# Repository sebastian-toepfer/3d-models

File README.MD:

A repo that contains my hardwares projects.
They are very simple, I am still learning. Most of the names are in German. My kicad stuff are mostly dangerous.

## ⚠️ Legal Disclaimer

This project and all associated hardware, firmware, and design files are provided **without any form of certification or regulatory approval**. They are intended **solely for private, educational, or research use**.

Any use of this project in a commercial, professional, or publicly accessible context may **require certification** (e.g. CE, FCC, RED) and compliance with national and international regulations.

It is **your sole responsibility** to ensure that any use, deployment, or modification of this project complies with applicable laws and technical standards, particularly in regard to **radio frequency emissions, electromagnetic compatibility (EMC), and product safety**.

The authors disclaim any liability for damages, legal issues, or regulatory violations resulting from the use of this project.

## License
until 2025/07/08: [CC0 1.0 Universal](https://creativecommons.org/publicdomain/zero/1.0/)  
from 2025/07/08 mutli licenses, see [LICENSE](LICENSE)

I'm making this move to express that the purpose of this repo is no longer just 3d (creative) content, but also includes PCBs and firmware.

## Structure

| folder                                               | description |
|------------------------------------------------------|-------------|
|projects                                              | contains the project, each is an umbrella to stuff for the same problem |
|projects/Makefile                                     | create the hole project (e.g. generated 3mf, stl or generate step from the pcb, build the firmware, flash firmware) |
|projects/&lt;prjname&gt;/3d                           | contains 3d stuff for the project |
|projects/&lt;prjname&gt;/3d/3mf                       | 3mf files for the project (currently all should be printable) |
|projects/&lt;prjname&gt;/3d/openscad                  | contains the openscad files of the project |
|projects/&lt;prjname&gt;/3d/openscad/libs             | link to the shared 3d libs (see below) |
|projects/&lt;prjname&gt;/3d/openscad/models           | a openscad model with the full assemblied model for the project (like a full case with bottom and top part) |
|projects/&lt;prjname&gt;/3d/openscad/parts            | openscad models which use to create the hole model and must be printed |
|projects/&lt;prjname&gt;/3d/openscad/sharedparts      | link to the shared 3d parts (see below) |
|projects/&lt;prjname&gt;/3d/step                      | step files used by the projekt (like the pcb) |
|projects/&lt;prjname&gt;/3d/stl                       | stl files, some can be printed some are created from the step to be usable in openscad |
|projects/&lt;prjname&gt;/docs                         | some docs |
|projects/&lt;prjname&gt;/docs/assembly                | how to assembly the parts to create the model |
|projects/&lt;prjname&gt;/firmware                     | the source for the firmware |
|projects/&lt;prjname&gt;/firmware/Makefile            | to create and flash the firmware |
|projects/&lt;prjname&gt;/kicad                        | kicad stuff for the project |
|projects/&lt;prjname&gt;/kicad/libraries              | project specific kicad stuff |
|projects/&lt;prjname&gt;/kicad/libraries/footprints   | custom footprints |
|projects/&lt;prjname&gt;/kicad/<kicadproject>         | the kicad project (or project's if we need more than one pcb) for the project |
|projects/&lt;prjname&gt;tools                         | link to shared tools (see below)  |
|shared                                                | stuff has no clean project focus or can be used by more than one project (subfolders should be linked into the projects if needed!)  |
|shared/3d/parts                                       | 3d parts can be used in more than one project  |
|shared/3d/libs                                        | 3d libs or reusable functions  |
|shared/3d/things                                      | 3d models of real existing things (like a speaker, a screen) |
|shared/tools                                          | tools without any project scope (like extract pinmapping from schematic and generate header and board.c) |

all parts are optional, this means a project with only 3d parts must not contains a firmware or a kicad folder.
bigger projects can contains projects it self!

a project should contains at least one Makefile to build it. if no Makefile in a project it means that it not generate or build anything (like tutorials).

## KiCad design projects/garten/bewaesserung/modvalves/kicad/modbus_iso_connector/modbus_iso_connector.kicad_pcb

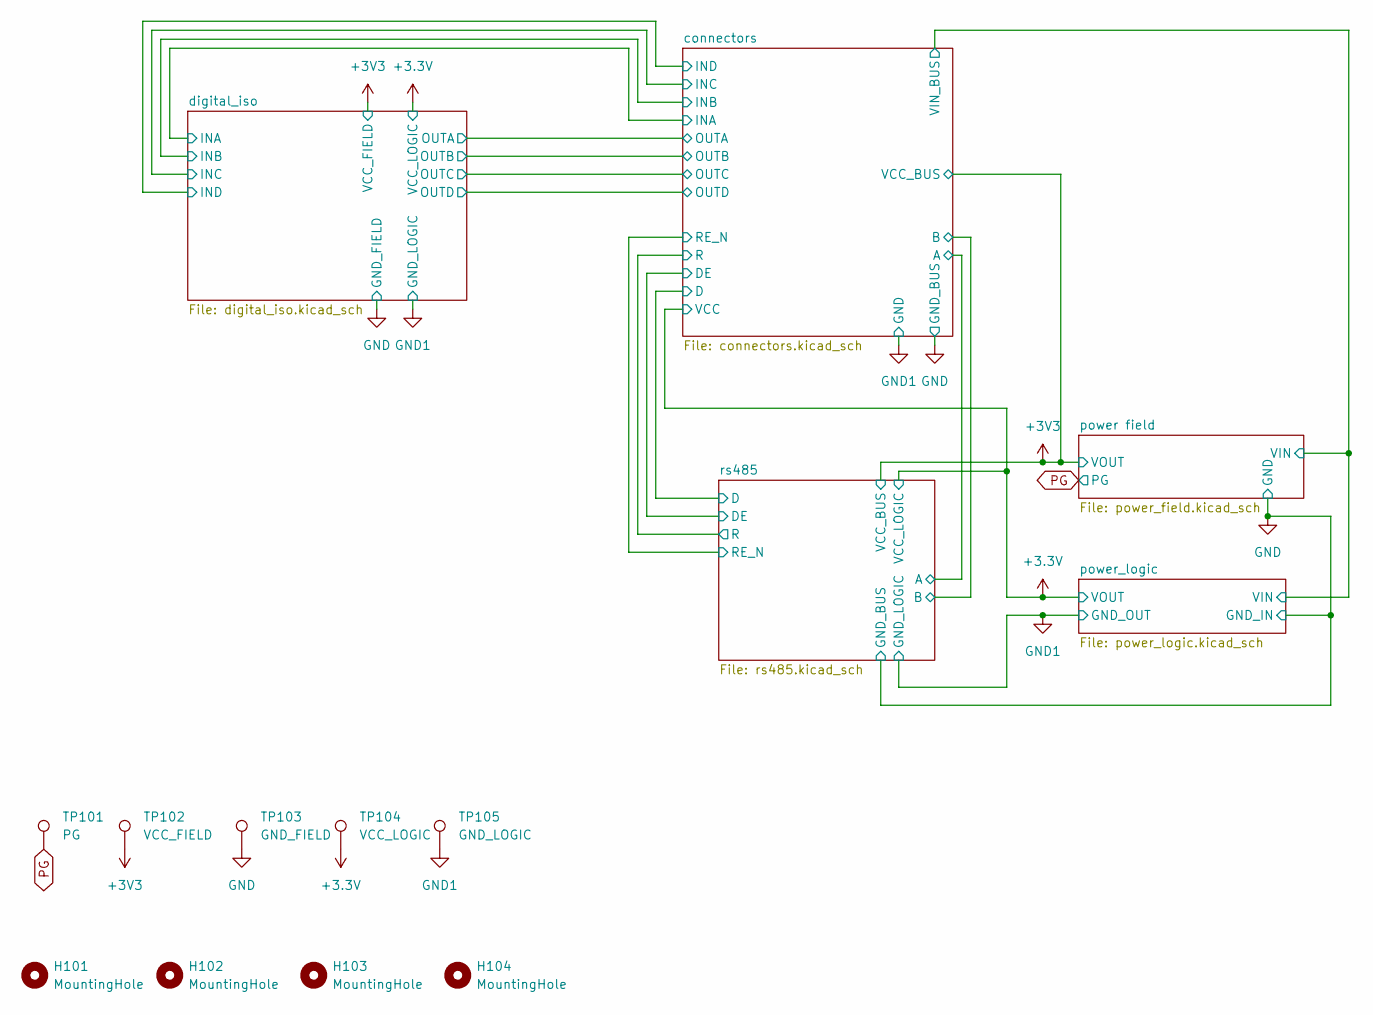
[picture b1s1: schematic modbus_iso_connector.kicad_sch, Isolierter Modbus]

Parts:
H101, H102, H103, H104: MountingHole; MountingHole_3.2mm_M3
TP101: PG; TestPoint_Pad_1.5x1.5mm
TP102: VCC_FIELD; TestPoint_Pad_1.5x1.5mm
TP103: GND_FIELD; TestPoint_Pad_1.5x1.5mm
TP104: VCC_LOGIC; TestPoint_Pad_1.5x1.5mm
TP105: GND_LOGIC; TestPoint_Pad_1.5x1.5mm

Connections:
+3.3V: TP104.1; also elsewhere on the board
+3V3: TP102.1; also elsewhere on the board
GND: TP103.1; also elsewhere on the board
GND1: TP105.1; also elsewhere on the board
PG: TP101.1; also elsewhere on the board

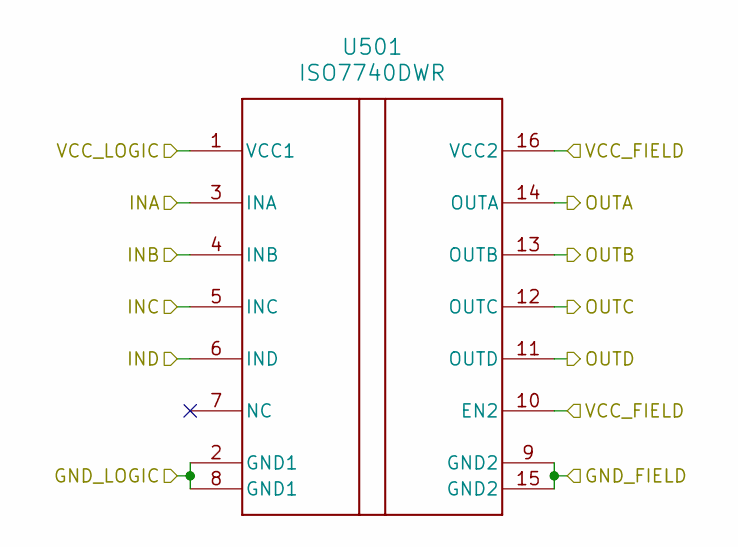
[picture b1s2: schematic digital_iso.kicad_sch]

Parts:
U501: ISO7740DWR; DW0016B_N

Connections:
+3.3V: U501.1 (VCC1); also elsewhere on the board
+3V3: U501.10 (EN2), U501.16 (VCC2); also elsewhere on the board
/connectors/INA: U501.3 (INA); also elsewhere on the board
/connectors/INB: U501.4 (INB); also elsewhere on the board
/connectors/INC: U501.5 (INC); also elsewhere on the board
/connectors/IND: U501.6 (IND); also elsewhere on the board
/connectors/OUTA: U501.14 (OUTA); also elsewhere on the board
/connectors/OUTB: U501.13 (OUTB); also elsewhere on the board
/connectors/OUTC: U501.12 (OUTC); also elsewhere on the board
/connectors/OUTD: U501.11 (OUTD); also elsewhere on the board
GND: U501.9 (GND2), U501.15 (GND2); also elsewhere on the board
GND1: U501.2 (GND1), U501.8 (GND1); also elsewhere on the board

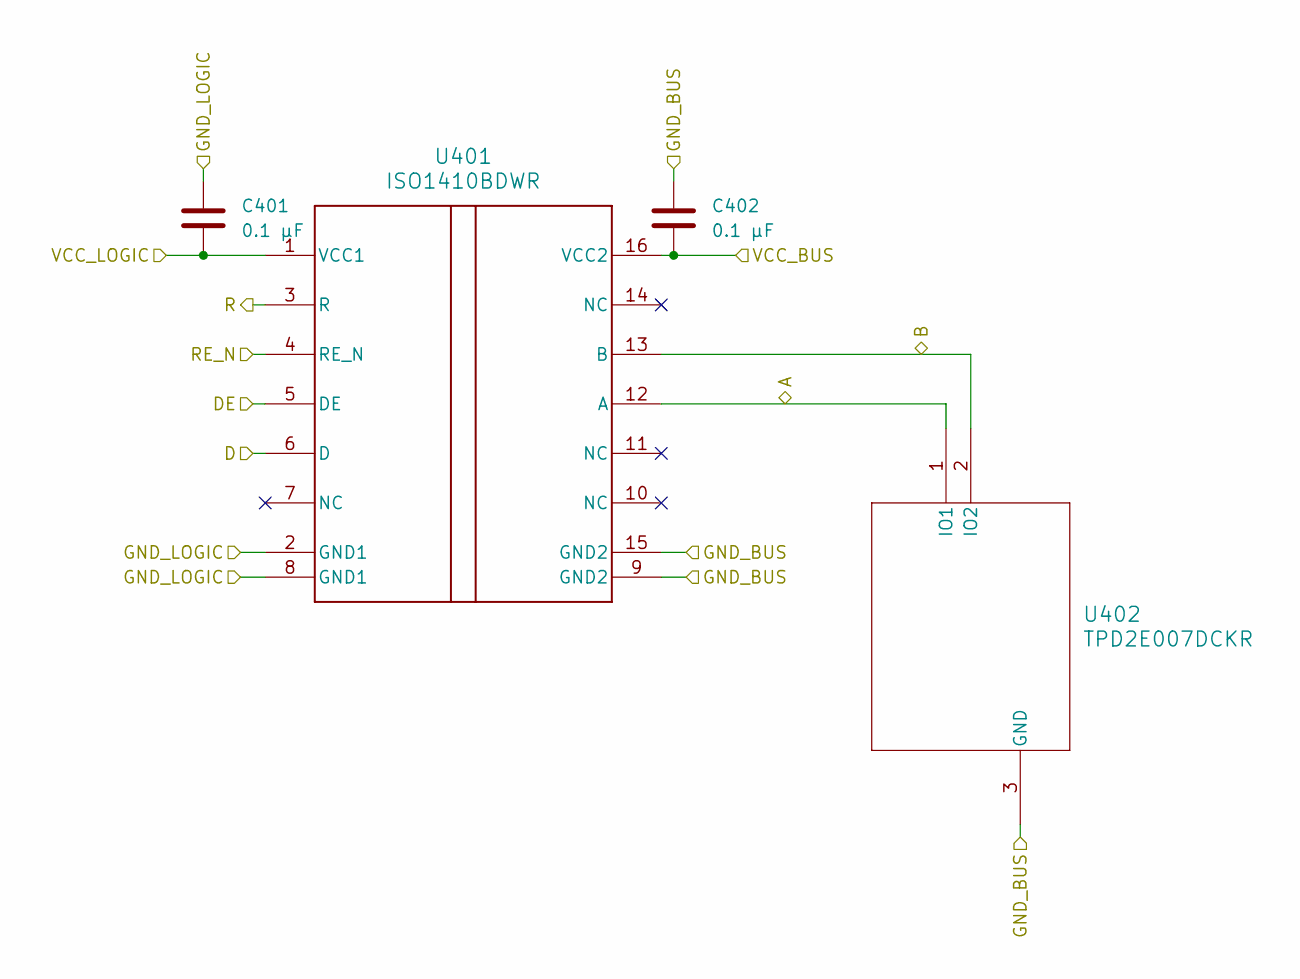
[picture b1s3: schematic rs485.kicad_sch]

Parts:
C401, C402: 0.1 µF; C_0603_1608Metric
U401: ISO1410BDWR; DW0016B_N
U402: TPD2E007DCKR; DCK3

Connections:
+3.3V: C401.2, U401.1 (VCC1); also elsewhere on the board
+3V3: C402.2, U401.16 (VCC2); also elsewhere on the board
/connectors/A: U401.12 (A), U402.1 (IO1); also elsewhere on the board
/connectors/B: U401.13 (B), U402.2 (IO2); also elsewhere on the board
/connectors/D: U401.6 (D); also elsewhere on the board
/connectors/DE: U401.5 (DE); also elsewhere on the board
/connectors/R: U401.3 (R); also elsewhere on the board
/connectors/RE_N: U401.4 (RE_N); also elsewhere on the board
GND: C402.1, U401.9 (GND2), U401.15 (GND2), U402.3 (GND); also elsewhere on the board
GND1: C401.1, U401.2 (GND1), U401.8 (GND1); also elsewhere on the board

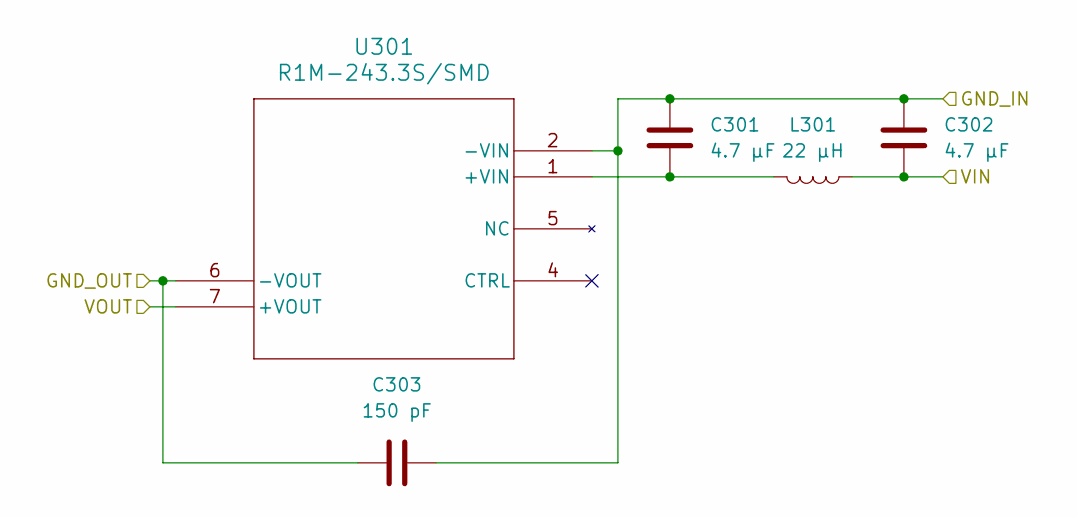
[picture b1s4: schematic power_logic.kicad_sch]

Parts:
C301, C302: 4.7 µF; C_0603_1608Metric
C303: 150 pF; C_Disc_D7.0mm_W4.0mm_P10.00mm; MPN DE1B3RA151KN4AP01F
L301: 22 µH; L_Wuerth_MAPI-4020; MPN 74438356220
U301: R1M-243.3S/SMD; R1M_SMD_RCP

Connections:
+3.3V: U301.7 (+VOUT); also elsewhere on the board
/connectors/VIN_BUS: C302.2, L301.1; also elsewhere on the board
GND: C301.1, C302.1, C303.2, U301.2 (-VIN); also elsewhere on the board
GND1: C303.1, U301.6 (-VOUT); also elsewhere on the board
unnamed: C301.2, L301.2, U301.1 (+VIN)

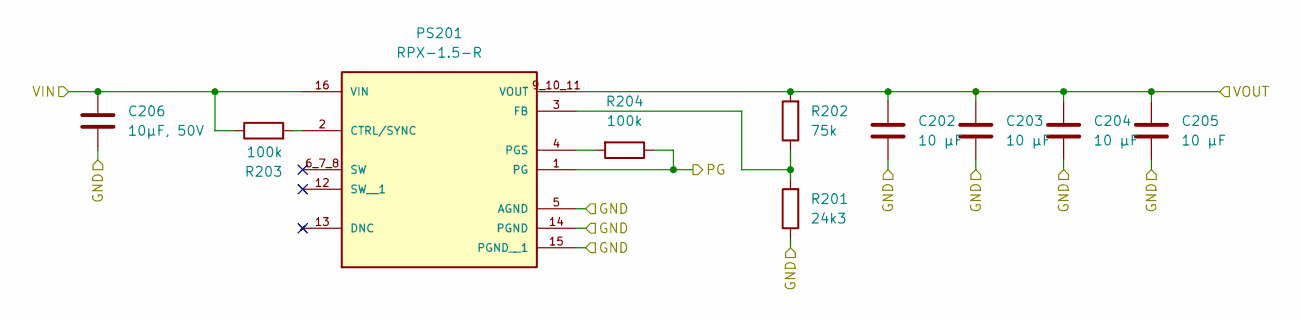
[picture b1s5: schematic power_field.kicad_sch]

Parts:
C202, C203, C204, C205: 10 µF; C_0603_1608Metric
C206: 10µF, 50V; C_1206_3216Metric
PS201: RPX-1.5-R; CONV_RPX-1.5-R; PARTREV 1/2022
R201: 24k3; R_0402_1005Metric
R202: 75k; R_0402_1005Metric
R203, R204: 100k; R_0402_1005Metric

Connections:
+3V3: C202.1, C203.1, C204.1, C205.2, PS201.9_10_11 (VOUT), R202.2; also elsewhere on the board
/connectors/VIN_BUS: C206.1, PS201.16 (VIN), R203.1; also elsewhere on the board
GND: C202.2, C203.2, C204.2, C205.1, C206.2, PS201.5 (AGND), PS201.14 (PGND), PS201.15 (PGND__1), R201.1; also elsewhere on the board
unnamed: PS201.2 (CTRL/SYNC), R203.2
unnamed: PS201.3 (FB), R201.2, R202.1
unnamed: PS201.4 (PGS), R204.2
PG: PS201.1 (PG), R204.1; also elsewhere on the board

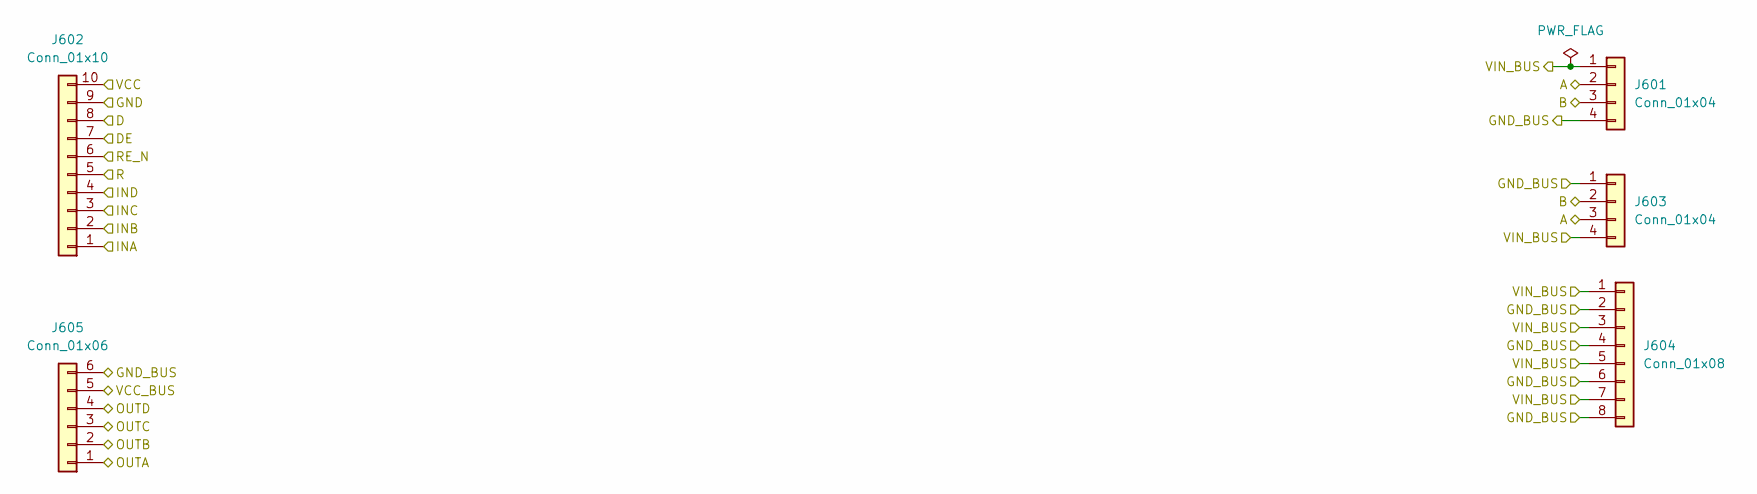
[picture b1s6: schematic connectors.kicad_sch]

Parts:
J601, J603: Conn_01x04; JST_XH_B4B-XH-A_1x04_P2.50mm_Vertical; MPN B4B-XH-A
J602: Conn_01x10; JST_XH_B10B-XH-A_1x10_P2.50mm_Vertical; MPN B10B-XH-A
J604: Conn_01x08; JST_XH_B8B-XH-A_1x08_P2.50mm_Vertical; MPN B8B-XH-A
J605: Conn_01x06; JST_XH_B6B-XH-A_1x06_P2.50mm_Vertical; MPN B6B-XH-A

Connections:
+3.3V: J602.10; also elsewhere on the board
+3V3: J605.5; also elsewhere on the board
/connectors/A: J601.2, J603.3; also elsewhere on the board
/connectors/B: J601.3, J603.2; also elsewhere on the board
/connectors/D: J602.8; also elsewhere on the board
/connectors/DE: J602.7; also elsewhere on the board
/connectors/INA: J602.1; also elsewhere on the board
/connectors/INB: J602.2; also elsewhere on the board
/connectors/INC: J602.3; also elsewhere on the board
/connectors/IND: J602.4; also elsewhere on the board
/connectors/OUTA: J605.1; also elsewhere on the board
/connectors/OUTB: J605.2; also elsewhere on the board
/connectors/OUTC: J605.3; also elsewhere on the board
/connectors/OUTD: J605.4; also elsewhere on the board
/connectors/R: J602.5; also elsewhere on the board
/connectors/RE_N: J602.6; also elsewhere on the board
/connectors/VIN_BUS: J601.1, J603.4, J604.1, J604.3, J604.5, J604.7; also elsewhere on the board
GND: J601.4, J603.1, J604.2, J604.4, J604.6, J604.8, J605.6; also elsewhere on the board
GND1: J602.9; also elsewhere on the board

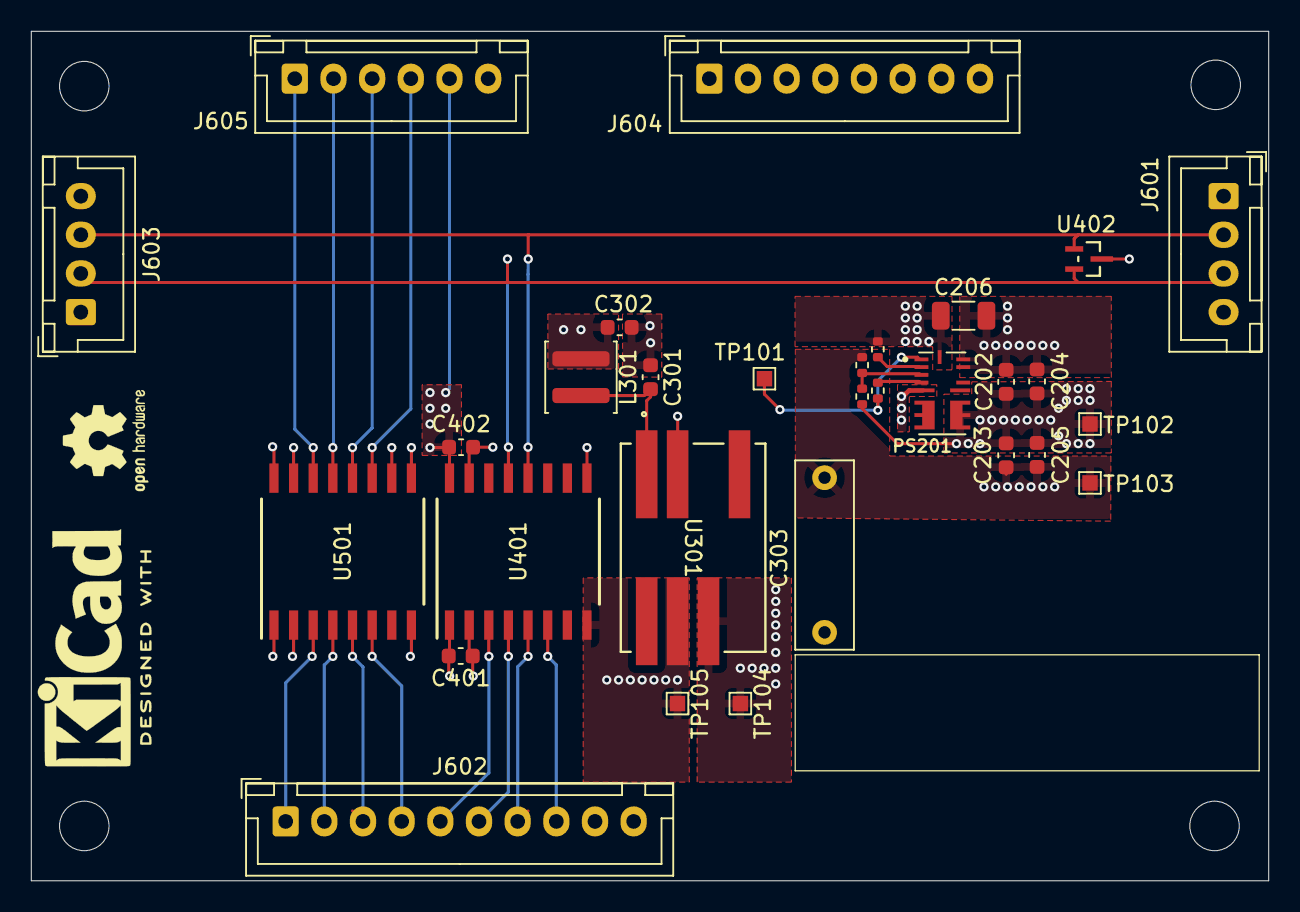
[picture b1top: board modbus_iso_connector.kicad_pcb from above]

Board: 4 copper layers, 80.0 x 54.9 mm, 34 parts (0 on the bottom side), 24 nets.

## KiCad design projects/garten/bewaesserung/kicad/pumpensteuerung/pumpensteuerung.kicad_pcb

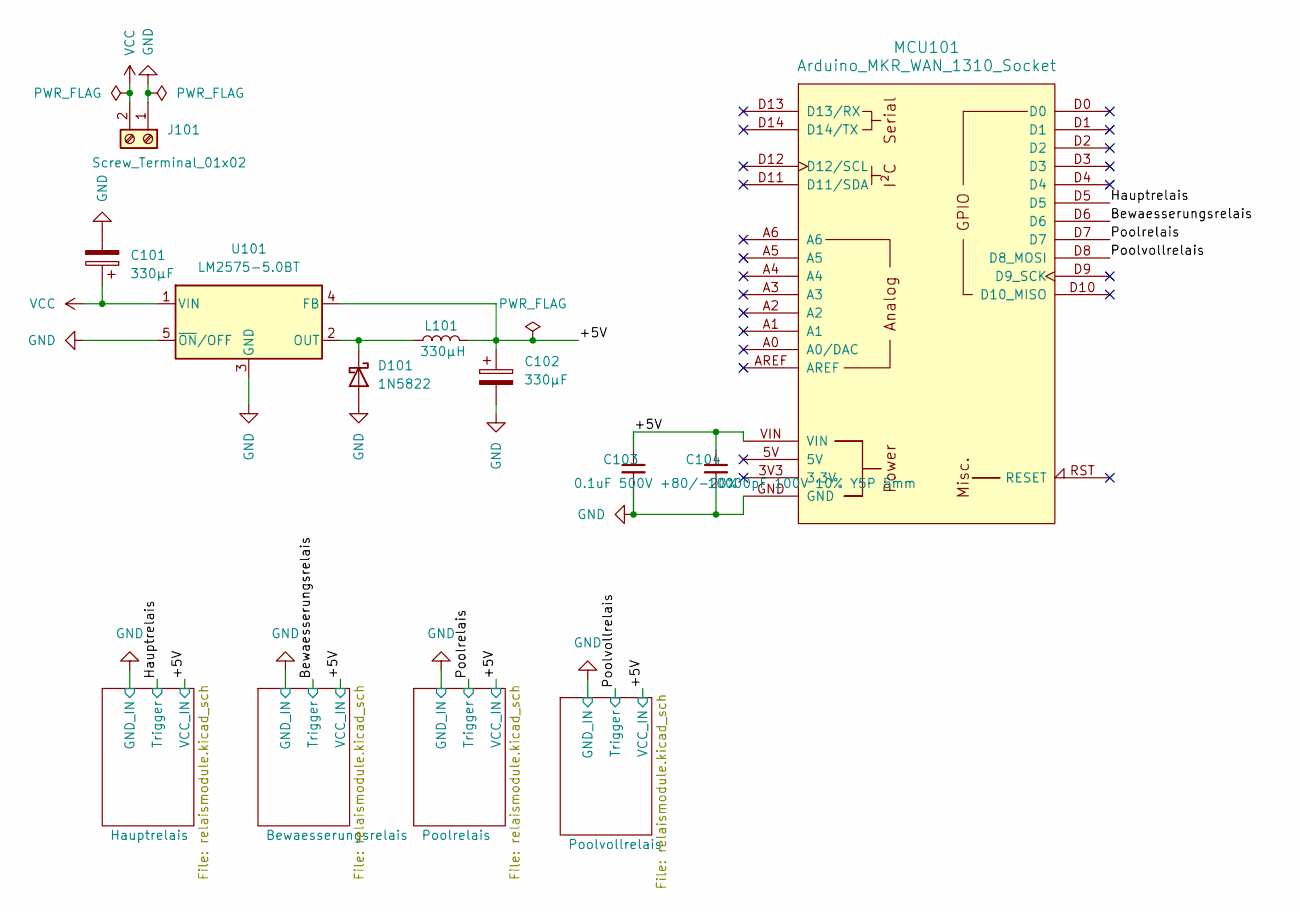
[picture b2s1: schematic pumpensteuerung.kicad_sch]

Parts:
C101, C102: 330µF; CP_Radial_D8.0mm_P2.50mm; MPN ECA-1CM331
C103: 0.1uF 500V +80/-20%; C_Disc_D5.0mm_W2.5mm_P5.00mm; MPN S104Z93Z5VL83L0R
C104: 10000pF 100V 10% Y5P 5mm; C_Disc_D5.0mm_W2.5mm_P5.00mm; MPN D103K43Y5PH6TJ5R
D101: 1N5822; D_DO-201AD_P15.24mm_Horizontal; MPN 1N5822
J101: Screw_Terminal_01x02; MKDSN 1,5_2-5,08; MPN 1729128
L101: 330µH; L_Radial_D8.7mm_P5.00mm_Fastron_07HCP; MPN DRC-V-331K
MCU101: Arduino_MKR_WAN_1310_Socket; Arduino_MKR_FOX_1200_Socket; MPN ABX00029
U101: LM2575-5.0BT; TO-220-5_Vertical; MPN LM2575-5.0WT

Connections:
/+5V: C102.1, C103.1, C104.1, L101.2, MCU101.VIN, U101.4 (FB); also elsewhere on the board
/Bewaesserungsrelais: MCU101.D6; also elsewhere on the board
/Hauptrelais: MCU101.D5; also elsewhere on the board
/Poolrelais: MCU101.D7; also elsewhere on the board
/Poolvollrelais: MCU101.D8 (D8_MOSI); also elsewhere on the board
GND: C101.2, C102.2, C103.2, C104.2, D101.2 (A), J101.1, MCU101.GND, U101.3 (GND), U101.5 (~ON/OFF); also elsewhere on the board
unnamed: D101.1 (K), L101.1, U101.2 (OUT)
VCC: C101.1, J101.2, U101.1 (VIN)

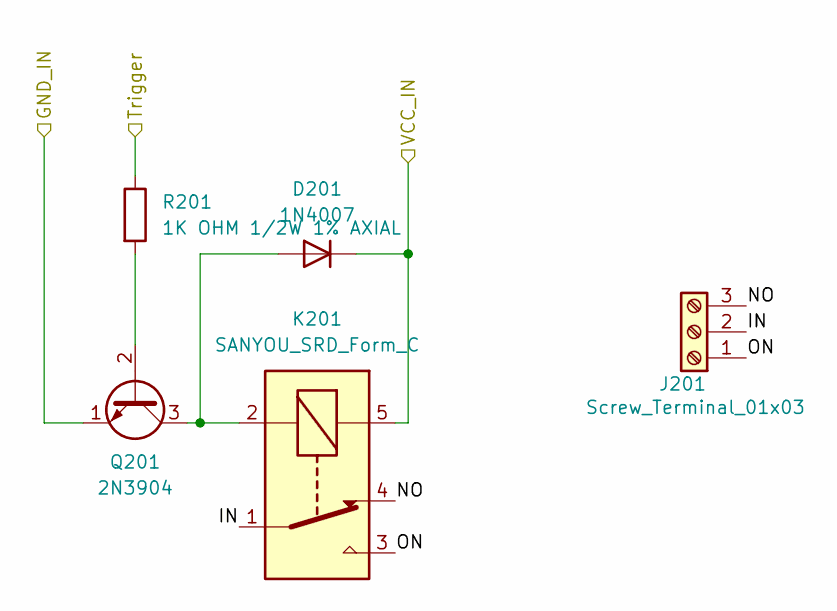
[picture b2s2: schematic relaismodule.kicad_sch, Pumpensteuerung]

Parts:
D201: 1N4007; D_DO-41_SOD81_P7.62mm_Horizontal; MPN 1N4007
J201: Screw_Terminal_01x03; MKDSN 1,5_3-5,08; MPN 1729131
K201: SANYOU_SRD_Form_C; Relay_SPDT_SANYOU_SRD_Series_Form_C; MPN HF3FA/005-ZTF
Q201: 2N3904; TO-92_Inline; MPN 2N3904
R201: 1K OHM 1/2W 1% AXIAL; R_Axial_DIN0207_L6.3mm_D2.5mm_P7.62mm_Horizontal; MPN SFR25H0001001FA500

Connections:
/+5V: D201.1 (K), K201.5; also elsewhere on the board
/Hauptrelais: R201.1; also elsewhere on the board
/Hauptrelais/IN: J201.2, K201.1
/Hauptrelais/NO: J201.3, K201.4
/Hauptrelais/ON: J201.1, K201.3
GND: Q201.1 (E); also elsewhere on the board
unnamed: D201.2 (A), K201.2, Q201.3 (C)
unnamed: Q201.2 (B), R201.2

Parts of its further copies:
D301, D401, D501: 1N4007; D_DO-41_SOD81_P7.62mm_Horizontal; MPN 1N4007
J301, J401, J501: Screw_Terminal_01x03; MKDSN 1,5_3-5,08; MPN 1729131
K301, K401, K501: SANYOU_SRD_Form_C; Relay_SPDT_SANYOU_SRD_Series_Form_C; MPN HF3FA/005-ZTF
Q301, Q401, Q501: 2N3904; TO-92_Inline; MPN 2N3904
R301, R401, R501: 1K OHM 1/2W 1% AXIAL; R_Axial_DIN0207_L6.3mm_D2.5mm_P7.62mm_Horizontal; MPN SFR25H0001001FA500

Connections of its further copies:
/+5V: D301.1 (K), D401.1 (K), D501.1 (K), K301.5, K401.5, K501.5; also elsewhere on the board
/Bewaesserungsrelais: R301.1; also elsewhere on the board
/Bewaesserungsrelais/IN: J301.2, K301.1
/Bewaesserungsrelais/NO: J301.3, K301.4
/Bewaesserungsrelais/ON: J301.1, K301.3
/Poolrelais: R401.1; also elsewhere on the board
/Poolrelais/IN: J401.2, K401.1
/Poolrelais/NO: J401.3, K401.4
/Poolrelais/ON: J401.1, K401.3
/Poolvollrelais: R501.1; also elsewhere on the board
/Poolvollrelais/IN: J501.2, K501.1
/Poolvollrelais/NO: J501.3, K501.4
/Poolvollrelais/ON: J501.1, K501.3
GND: Q301.1 (E), Q401.1 (E), Q501.1 (E); also elsewhere on the board
unnamed: D301.2 (A), K301.2, Q301.3 (C)
unnamed: D401.2 (A), K401.2, Q401.3 (C)
unnamed: D501.2 (A), K501.2, Q501.3 (C)
unnamed: Q301.2 (B), R301.2
unnamed: Q401.2 (B), R401.2
unnamed: Q501.2 (B), R501.2

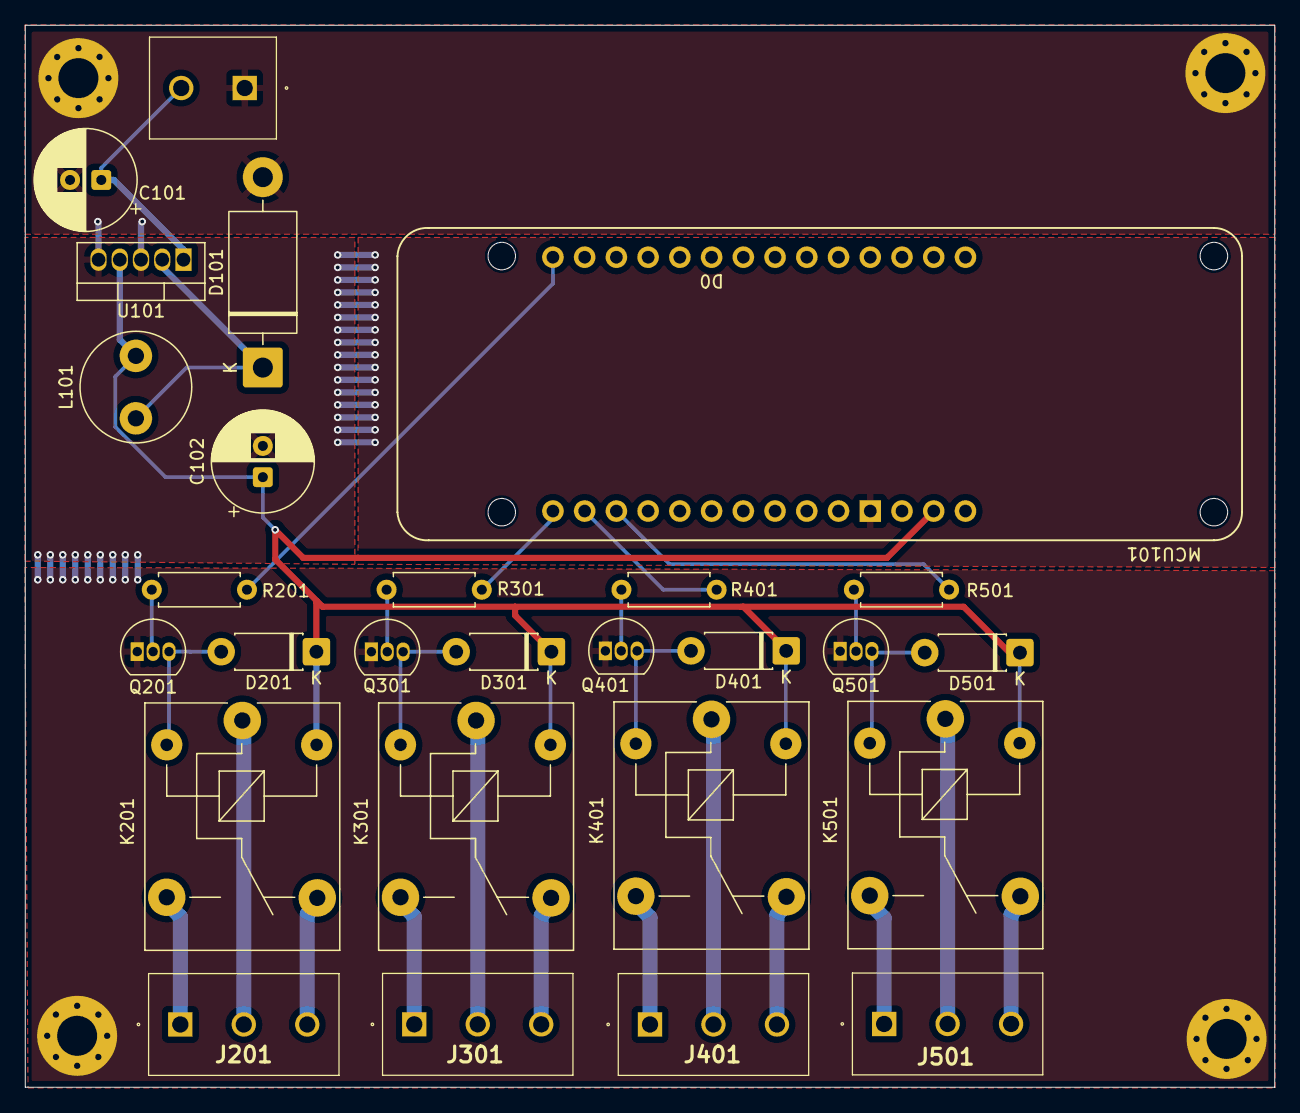
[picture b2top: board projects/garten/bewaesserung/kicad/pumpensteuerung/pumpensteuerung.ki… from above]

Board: 2 copper layers, 100.0 x 85.0 mm, 31 parts (0 on the bottom side), 28 nets.

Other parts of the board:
H101, H102, H103, H104: M3; MountingHole_3.2mm_M3_Pad_Via

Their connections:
GND: H101.1, H102.1, H103.1, H104.1; also elsewhere on the board

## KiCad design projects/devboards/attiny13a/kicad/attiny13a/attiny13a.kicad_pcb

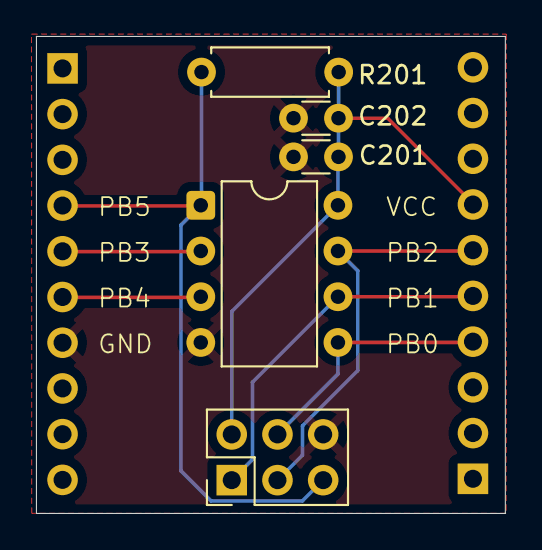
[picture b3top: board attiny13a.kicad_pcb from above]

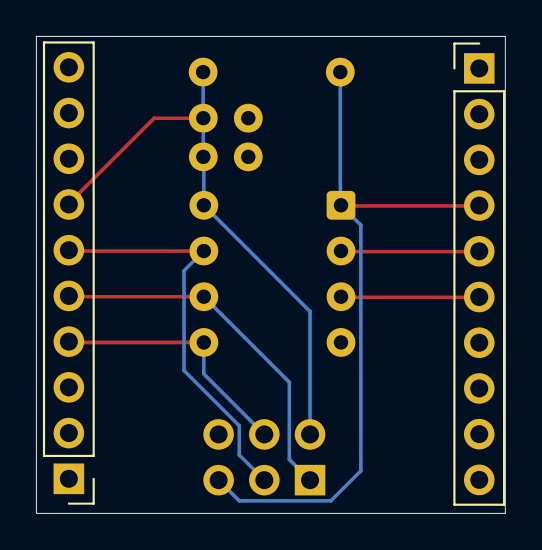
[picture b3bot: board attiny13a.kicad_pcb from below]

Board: 2 copper layers, 26.0 x 26.5 mm, 7 parts (2 on the bottom side), 8 nets.

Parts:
C201: 100 nF; C_Disc_D3.0mm_W1.6mm_P2.50mm
C202: 10 nF; C_Disc_D3.0mm_W1.6mm_P2.50mm
J201: Federkontakt; DIP-8_W7.62mm
J301: PinLeiste_Links; PinHeader_1x10_P2.54mm_Vertical
J302: PinLeiste_Rechts; PinHeader_1x10_P2.54mm_Vertical
J401: USBasp; PinHeader_2x03_P2.54mm_Vertical
R201: 10k; R_Axial_DIN0207_L6.3mm_D2.5mm_P7.62mm_Horizontal

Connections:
+5V: C201.2, C202.2, J201.8, J302.7, J401.2, R201.1
/PICO: J201.5, J302.4, J401.4
/POCI: J201.6, J302.5, J401.1
/SCK: J201.7, J302.6, J401.3
/USBasp/RESET: J201.1, J301.4, J401.5, R201.2
/breadboad_pins/PB3: J201.2, J301.5
/breadboad_pins/PB4: J201.3, J301.6
GND: C201.1, C202.1, J201.4, J301.7, J401.6

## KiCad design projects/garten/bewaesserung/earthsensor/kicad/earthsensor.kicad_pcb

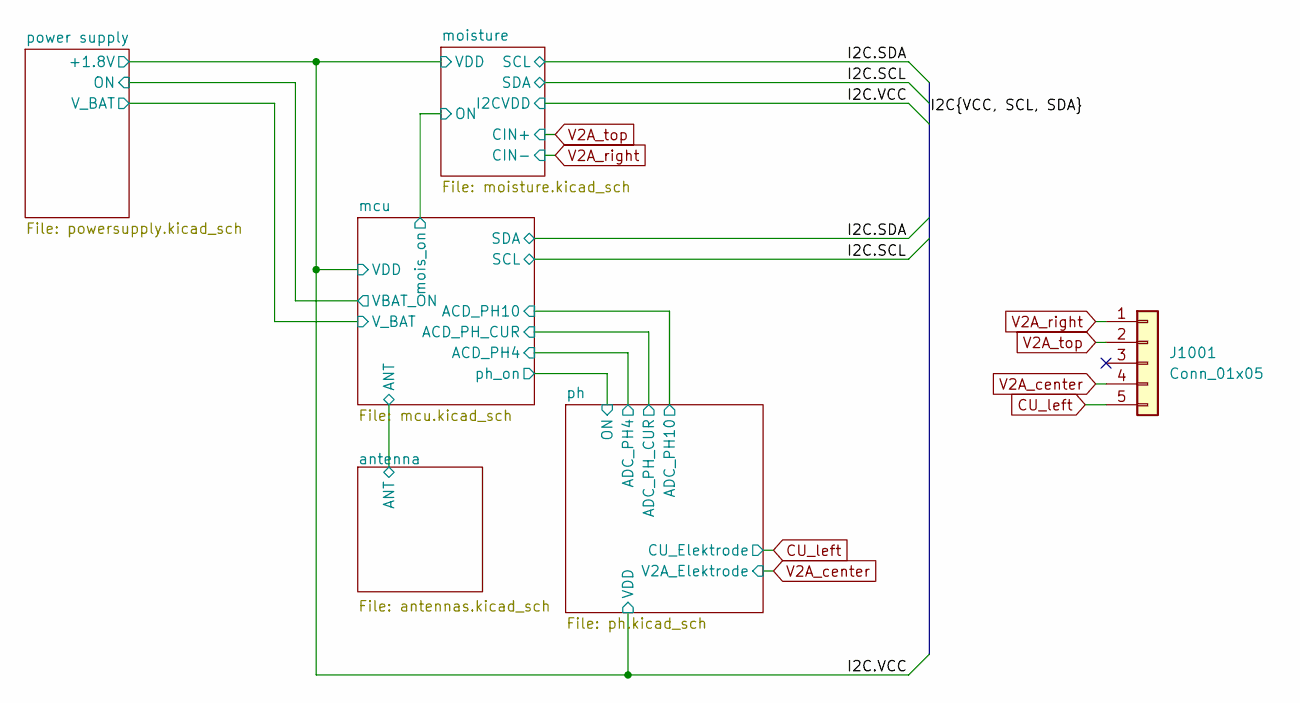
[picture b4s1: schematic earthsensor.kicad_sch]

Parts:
J1001: Conn_01x05; 691412320005; MPN 691412320005

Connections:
CU_left: J1001.5; also elsewhere on the board
V2A_center: J1001.4; also elsewhere on the board
V2A_right: J1001.1; also elsewhere on the board
V2A_top: J1001.2; also elsewhere on the board

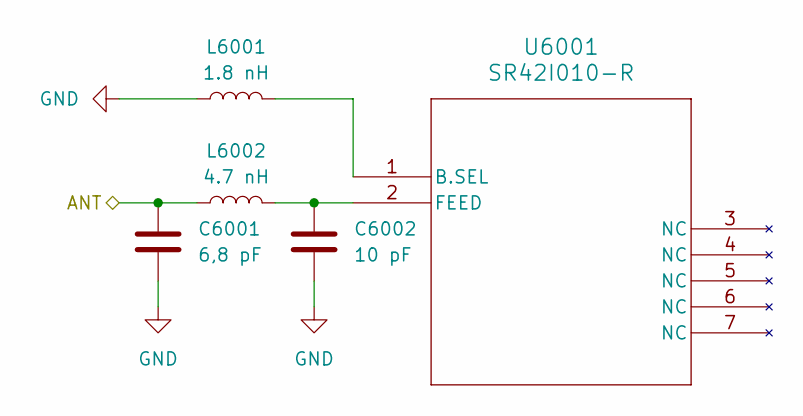
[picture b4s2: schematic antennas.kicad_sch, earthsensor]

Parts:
C6001: 6,8 pF; C_0402_1005Metric; MPN GJM1555C1H6R8WB01D
C6002: 10 pF; C_0402_1005Metric; MPN GJM1555C1H100GB01D
L6001: 1.8 nH; L_0402_1005Metric; MPN LQW15AN1N8C00D
L6002: 4.7 nH; L_0402_1005Metric; MPN LQW15AN4N7B00D
U6001: SR42I010-R; SR42I010-R_ANT; MPN SR42I010-R

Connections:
/antenna/ANT: C6001.2, L6002.1; also elsewhere on the board
GND: C6001.1, C6002.1, L6001.1; also elsewhere on the board
unnamed: L6001.2, U6001.1 (B.SEL)
unnamed: C6002.2, L6002.2, U6001.2 (FEED)

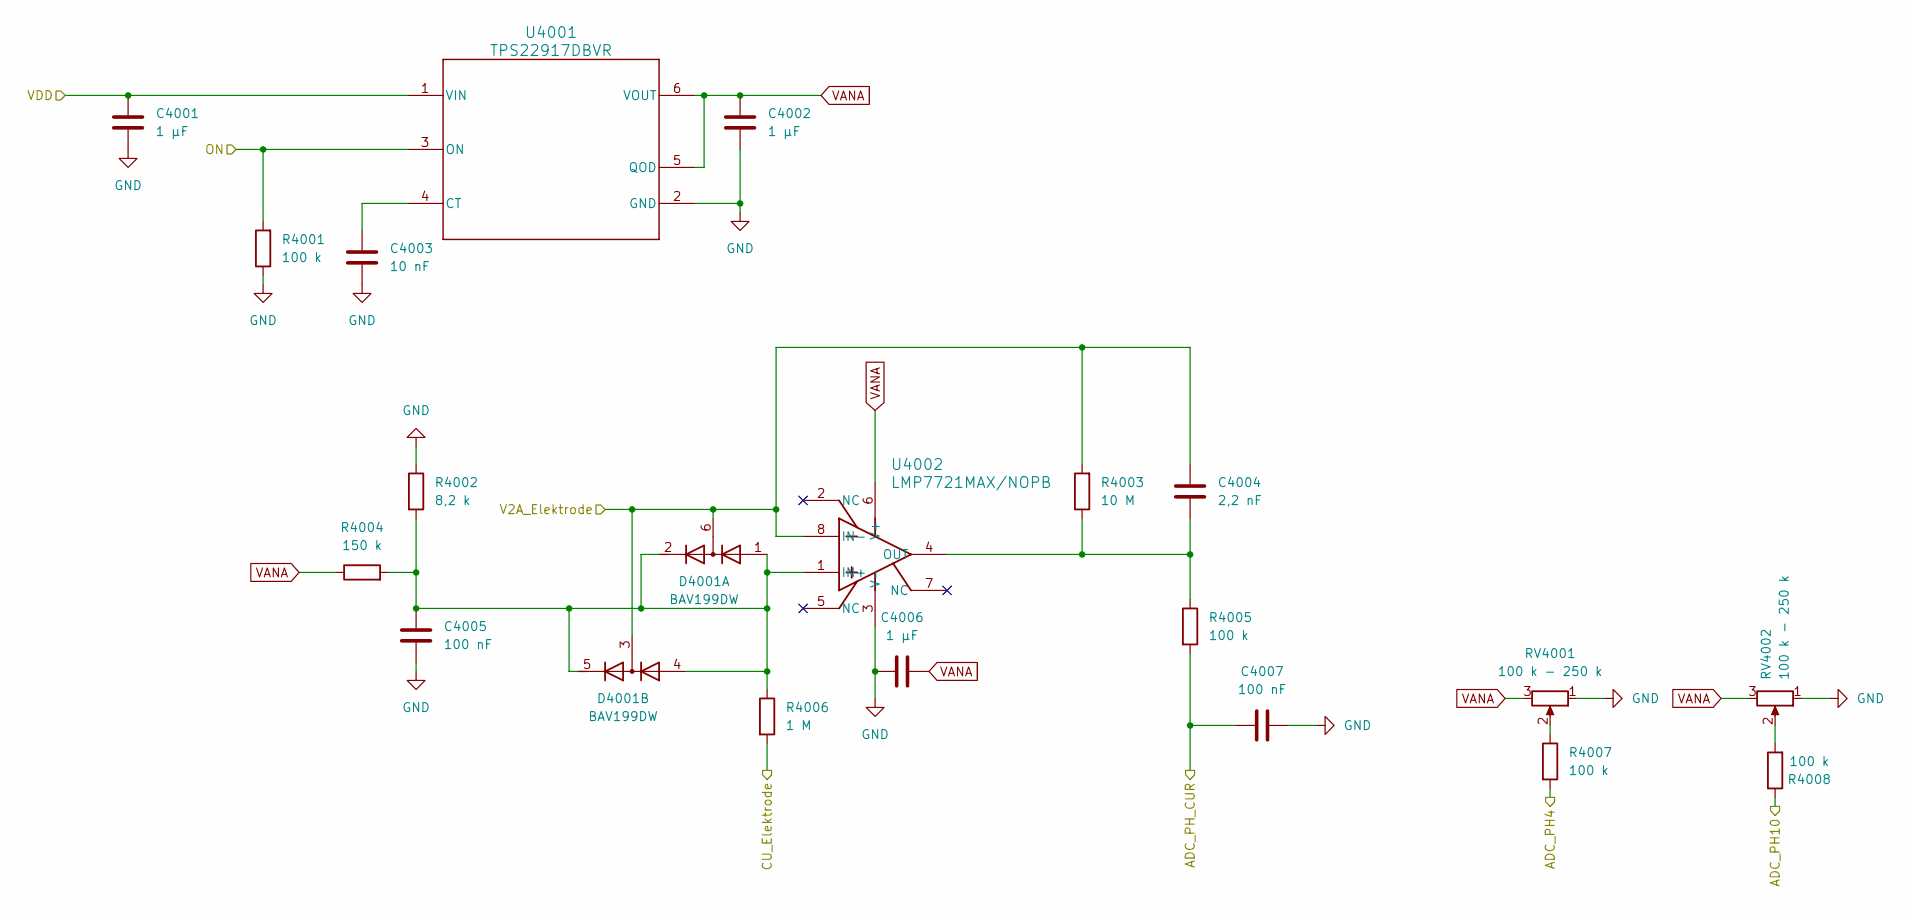
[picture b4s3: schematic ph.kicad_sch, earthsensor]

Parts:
C4001, C4002, C4006: 1 µF; C_0805_2012Metric; MPN GCJ21BR71H105KA01L
C4003: 10 nF; C_0805_2012Metric; MPN GRM2195C1H103FA01D
C4004: 2,2 nF; C_0805_2012Metric; MPN GRM2165C1H222GA01D
C4005, C4007: 100 nF; C_0805_2012Metric; MPN GCM21BR72A104KA37L
D4001: BAV199DW; SOT-363_SC-70-6; MPN BAV199S-QZ
R4001, R4005, R4007, R4008: 100 k; R_0402_1005Metric; MPN RN73H1ETTP1003B25
R4002: 8,2 k; R_0402_1005Metric; MPN RK73H1ETTP8201F
R4003: 10 M; R_0402_1005Metric; MPN RK73H1ETTP1005F
R4004: 150 k; R_0402_1005Metric; MPN RN73H1ETTP1503B25
R4006: 1 M; R_0402_1005Metric; MPN RK73H1ETTP1004F
RV4001, RV4002: 100 k - 250 k; Potentiometer_Bourns_3224W_Vertical; MPN 3224W-1-254E
U4001: TPS22917DBVR; DBV0006_N; MPN TPS22917DBVR
U4002: LMP7721MAX/NOPB; M08A; MPN LMP7721MAX/NOPB

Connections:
/mcu/ACD_PH4: R4007.2; also elsewhere on the board
/mcu/ACD_PH10: R4008.1; also elsewhere on the board
/mcu/ACD_PH_CUR: C4007.1, R4005.2; also elsewhere on the board
/mcu/ph_on: R4001.2, U4001.3 (ON); also elsewhere on the board
CU_left: R4006.2; also elsewhere on the board
GND: C4001.2, C4002.2, C4003.2, C4005.1, C4006.1, C4007.2, R4001.1, R4002.1, RV4001.1, RV4002.1, U4001.2 (GND), U4002.3 (V-); also elsewhere on the board
unnamed: C4005.2, D4001.1 (A1), D4001.2 (K2), D4001.4 (A3), D4001.5 (K4), R4002.2, R4004.2, R4006.1, U4002.1 (IN+)
unnamed: R4007.1, RV4001.2
unnamed: R4008.2, RV4002.2
unnamed: C4003.1, U4001.4 (CT)
unnamed: C4004.2, R4003.1, R4005.1, U4002.4 (OUT)
V2A_center: C4004.1, D4001.3 (K1A2), D4001.6 (K3A4), R4003.2, U4002.8 (IN-); also elsewhere on the board
VANA: C4002.1, C4006.2, R4004.1, RV4001.3, RV4002.3, U4001.5 (QOD), U4001.6 (VOUT), U4002.6 (V+)
VDD: C4001.1, U4001.1 (VIN); also elsewhere on the board
